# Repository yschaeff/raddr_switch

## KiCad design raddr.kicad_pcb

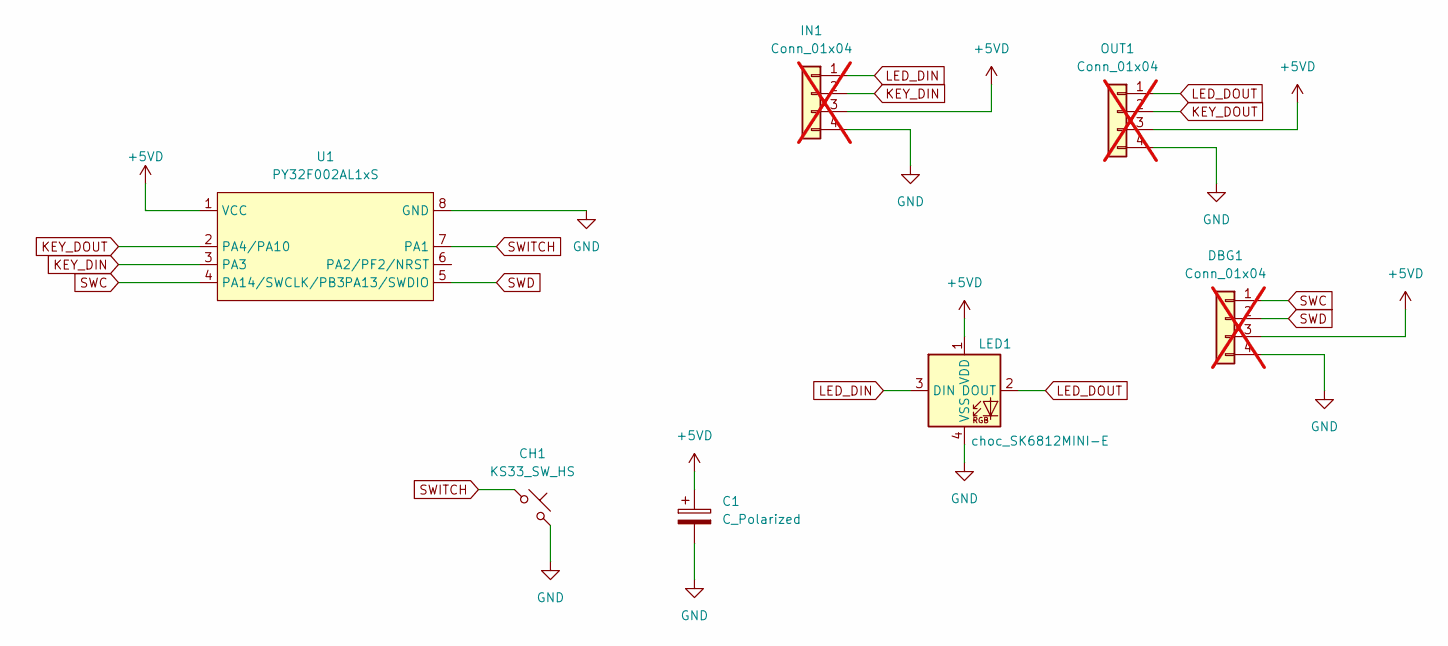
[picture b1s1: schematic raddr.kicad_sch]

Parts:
C1: C_Polarized; C_0603_1608Metric_Pad1.08x0.95mm_HandSolder
CH1: KS33_SW_HS; SW_KS33_HS_KS-2P02B01-02_HS_1u
DBG1: Conn_01x04; PinSocket_1x04_P2.54mm_Vertical; not fitted
IN1: Conn_01x04; PinSocket_1x04_P2.54mm_Vertical; not fitted
LED1: choc_SK6812MINI-E; LED_choc_6028R
OUT1: Conn_01x04; PinSocket_1x04_P2.54mm_Vertical; not fitted
U1: PY32F002AL1xS; SOP-8_3.9x4.9mm_P1.27mm

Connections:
+5VD: C1.1, DBG1.3, IN1.3, LED1.1 (VDD), OUT1.3, U1.1 (VCC)
GND: C1.2, CH1.2, DBG1.4, IN1.4, LED1.4 (VSS), OUT1.4, U1.8 (GND)
KEY_DIN: IN1.2, U1.3 (PA3)
KEY_DOUT: OUT1.2, U1.2 (PA4/PA10)
LED_DIN: IN1.1, LED1.3 (DIN)
LED_DOUT: LED1.2 (DOUT), OUT1.1
SWC: DBG1.1, U1.4 (PA14/SWCLK/PB3)
SWD: DBG1.2, U1.5 (PA13/SWDIO)
SWITCH: CH1.1, U1.7 (PA1)

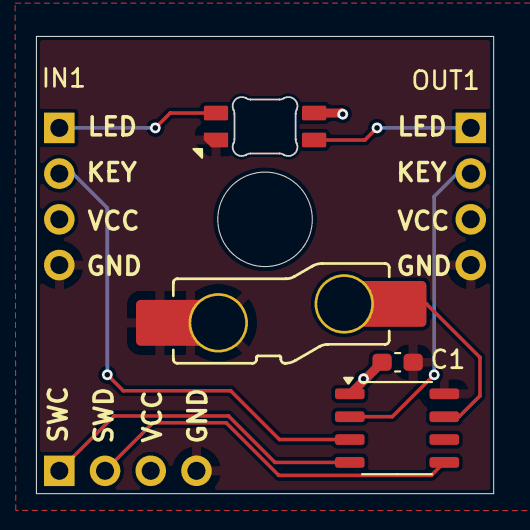
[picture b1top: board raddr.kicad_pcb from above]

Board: 2 copper layers, 25.3 x 25.3 mm, 7 parts (0 on the bottom side), 9 nets.

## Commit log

2024-09-10 empty project
2024-09-10 padauk MCU libary
2024-09-10 Place all components
2024-09-10 Footprints
2024-09-11 add traces
2024-09-11 these files may be important?
2024-09-11 ignore file
2024-09-11 Muck around about traces
2024-09-12 WFP correction factor
2024-09-12 Add design rules.
    Took them from: https://github.com/labtroll/KiCad-DesignRules/tree/main/JLCPCB
2024-09-12 split connector
2024-09-12 silk screen
2024-09-14 Silk screen adjustments.
2024-09-14 Add description of the K-NINE protocol for RABIES.
2024-09-14 fixes to K-NINE doc
2024-09-14 Some clarifications.
2024-09-14 overhaul
    - Align on grid
    - fillet
    - shring X dim
    - center button
    - remove extra bttn holes
2024-09-14 Mark pads as catellated
2024-09-14 No CourtYard no problems!
2024-09-15 Also mark single pins at the bottom as DNP
2024-09-15 Increase distance of board perimeter to pad to eliminate warning.
2024-09-15 Fix thermal relieve issues by rotating spokes for pins near board edge.
2024-09-18 firmware proposal for RABI
2024-09-19 Akela implementation.
2024-09-19 Implement flip.
2024-10-30 Redesign
2024-10-30 fix power plane
2024-10-31 silk screen and stuff
2024-11-07 pack.c: This is not Python
2024-11-07 Make it more like C. It now only complains about not having pins defined
2024-11-13 Pack & Wolf: Fix bug: Wait only once for low period. Add externals for gpio_set/gpio_get/sleep_ns and SOME_INPUT
    This make it compile without complaining. Now we can start implementing a welp.
2024-11-13 Add test directory, Makefile and basic test. It does something I guess
2024-11-14 Expand tests
    Also HOWL state was not actually a state.
2024-11-14 test n
2024-11-14 reinstate BARK state Actually test the thing
